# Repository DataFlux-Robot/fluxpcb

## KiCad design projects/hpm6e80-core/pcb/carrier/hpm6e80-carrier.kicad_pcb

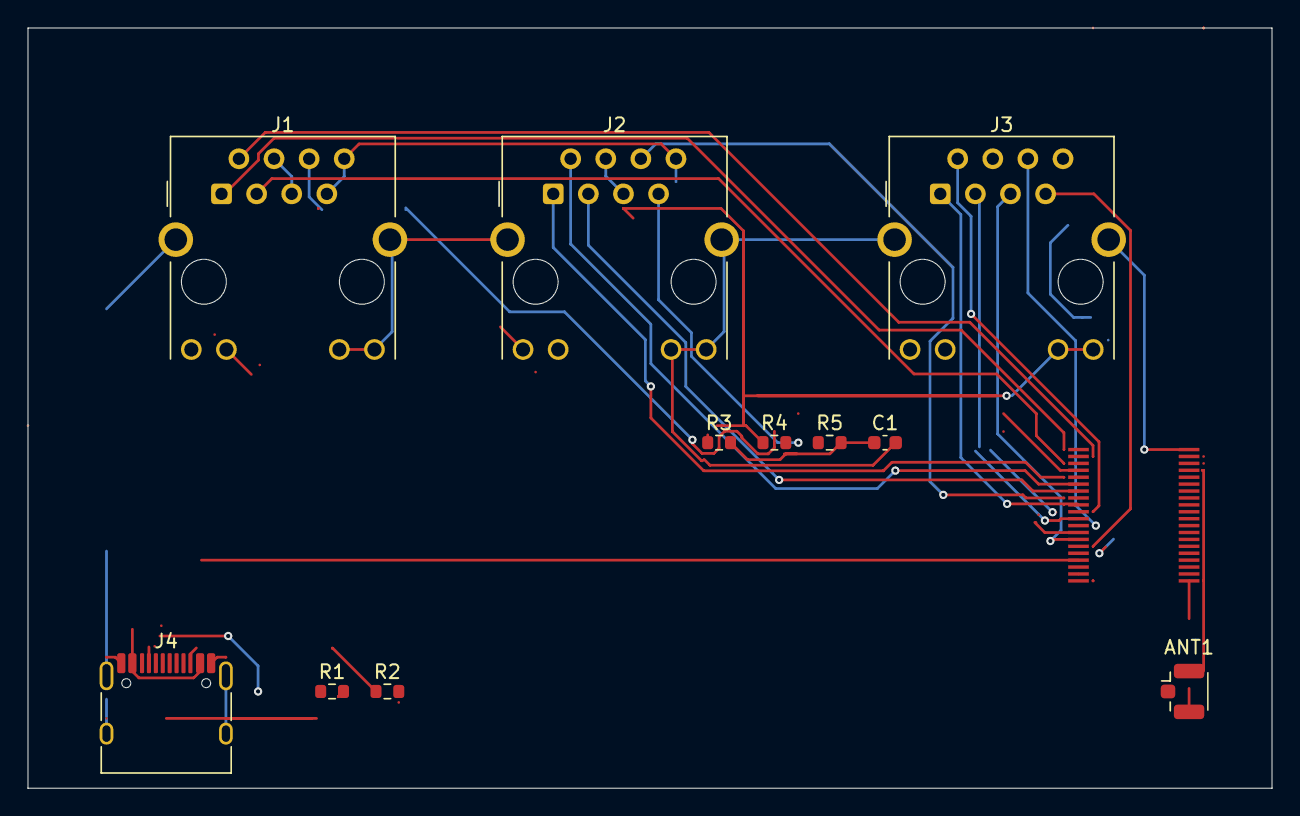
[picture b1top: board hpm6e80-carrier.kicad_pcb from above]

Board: 2 copper layers, 90.0 x 55.0 mm, 11 parts (0 on the bottom side), 9 nets.

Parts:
ANT1: U.FL-ANT; U.FL_Hirose_U.FL-R-SMT-1_Vertical
C1: 1nF/2kV; C_0603_1608Metric
J1: RJ45-ECAT-P0; RJ45_Hanrun_HR911105A_Horizontal
J2: RJ45-ECAT-P1; RJ45_Hanrun_HR911105A_Horizontal
J3: RJ45-TSN-GBE; RJ45_Hanrun_HR911105A_Horizontal
J4: USB-C-5V; USB_C_Receptacle_HRO_TYPE-C-31-M-12
R1, R2: 5.1k; R_0603_1608Metric
R3, R4, R5: 75R; R_0603_1608Metric

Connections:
BS_A: J1.4, J1.5, J2.4, J2.5, J3.11, J3.12, R3.1, R4.1
BS_B: J1.7, J1.8, J2.7, J2.8, R5.1
BS_TERM: C1.1, R3.2, R4.2, R5.2
CC1: J4.A5, R1.1
CC2: J4.B5, R2.1
GND: ANT1.2, C1.2, J1.11, J1.12, J1.SH, J2.11, J2.12, J2.SH, J3.SH, J4.A1, J4.A12, J4.B1, J4.B12, J4.SH, R1.2, R2.2
LED_ECAT1: J1.9, J2.9
LED_ECAT2: J1.10, J2.10
VBUS_5V: J4.A4, J4.A9, J4.B4, J4.B9
